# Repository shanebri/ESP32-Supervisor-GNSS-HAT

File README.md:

# ESP32 Supervisor + GNSS HAT

Raspberry Pi HAT with an ESP32-C6 supervisor, u-blox MAX-M10S GNSS receiver, and HAT ID EEPROM.

Open `hardware/Argus-RPI-HAT.kicad_pro` in KiCad 10. The folder includes the routed four-layer PCB, schematics, and custom footprints.

DRC/ERC reports are in `hardware/checks/` and use the project's configured rules. The board has not been hardware-tested; verify the fabrication stack-up and USB/GNSS impedance before ordering.

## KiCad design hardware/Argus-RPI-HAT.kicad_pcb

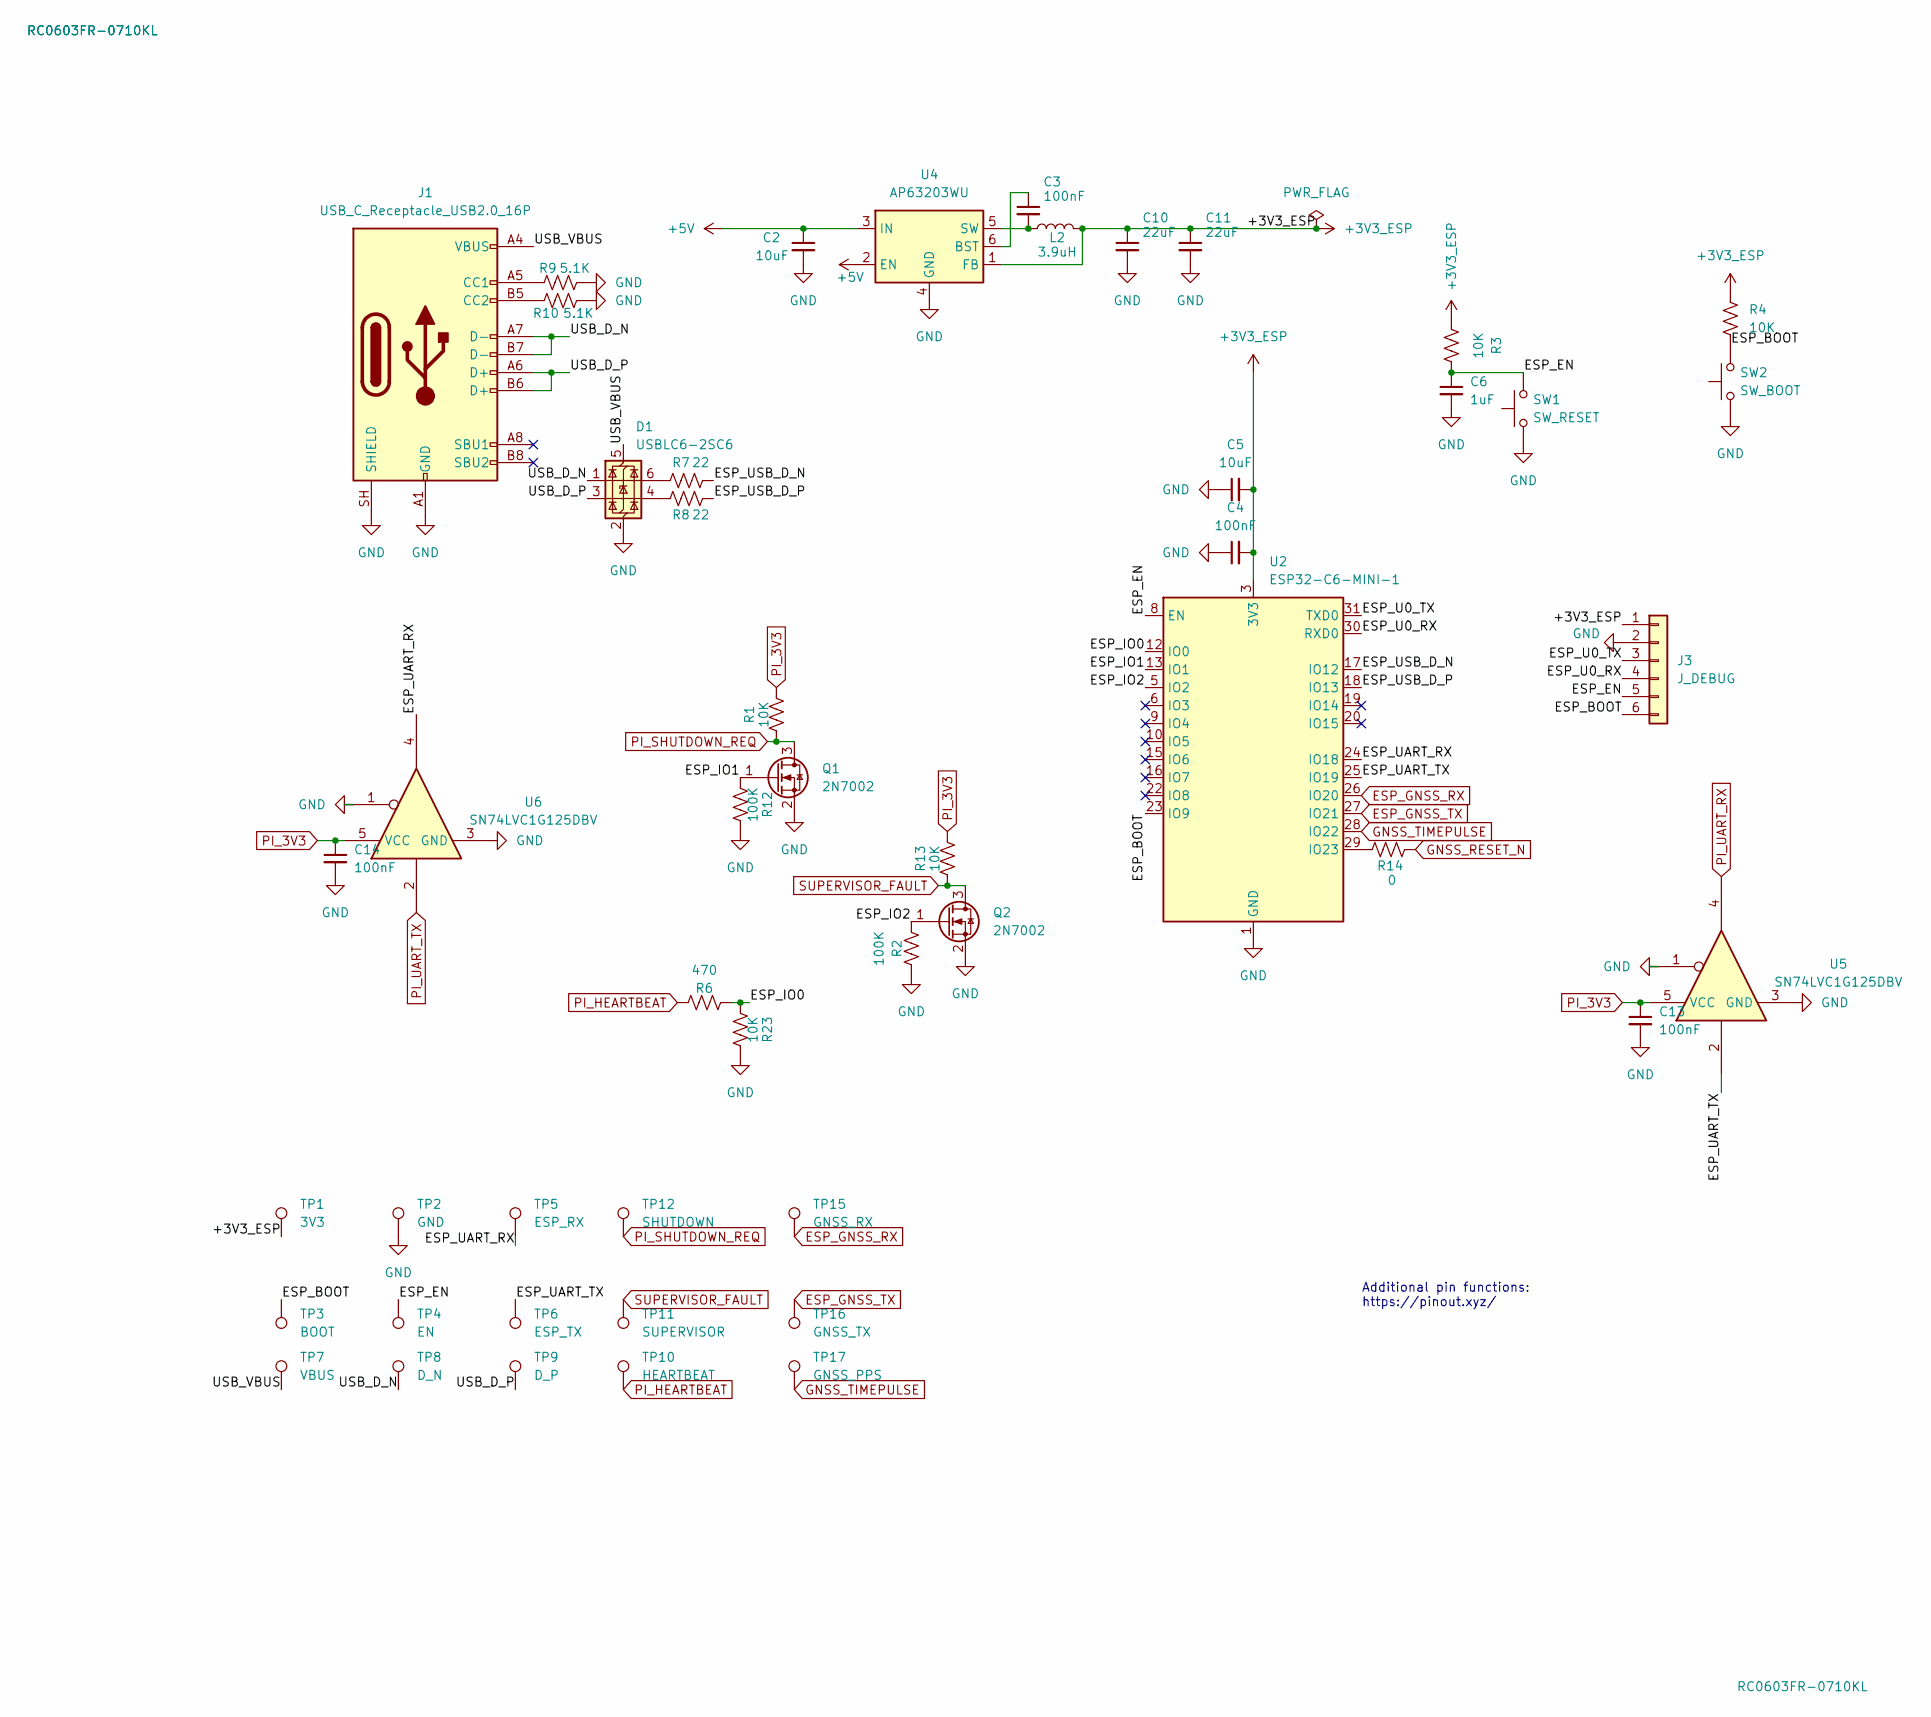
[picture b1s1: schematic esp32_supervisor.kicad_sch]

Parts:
C2: 10uF; C_0603_1608Metric; Rated Voltage 16V; Tolerance 10%; MPN GRM31CR71C106KA12L
C3, C4, C13, C14: 100nF; C_0603_1608Metric; Rated Voltage 50V; Tolerance 10%; MPN C0603C104K5RACTU
C5: 10uF; C_0805_2012Metric; Rated Voltage 10V; Tolerance 10%; MPN GRM21BR71A106KE51L
C6: 1uF; C_0603_1608Metric; Rated Voltage 16V; Tolerance 10%; MPN GRM188R71C105KA12D
C10, C11: 22uF; C_1206_3216Metric; MPN GRM31CR71A226ME15L
D1: USBLC6-2SC6; SOT-23-6; MPN USBLC6-2SC6
J1: USB_C_Receptacle_USB2.0_16P; USB_C_HRO_TYPE-C-31-M-12_EdgeSilk; MPN TYPE-C-31-M-12
J3: J_DEBUG; PinHeader_1x06_P2.54mm_Vertical; MPN TSW-106-07-G-S
L2: 3.9uH; L_Wurth_WE-PD2SR-7850
Q1, Q2: 2N7002; SOT-23; MPN 2N7002,215
R1, R3, R4, R13, R23: 10K; R_0603_1608Metric; MPN RC0603FR-0710KL
R2, R12: 100K; R_0603_1608Metric; MPN RC0603FR-07100KL
R6: 470; R_0603_1608Metric; MPN RC0603FR-07470RL
R7, R8: 22; R_0603_1608Metric; MPN RC0603FR-0722RL
R9, R10: 5.1K; R_0603_1608Metric; MPN RC0603FR-075K1L
R14: 0; R_0603_1608Metric; MPN RC0603JR-070RL
SW1: SW_RESET; SW_SPST_TL3305A; MPN TL3305AF160QG
SW2: SW_BOOT; SW_SPST_TL3305A; MPN TL3305AF160QG
TP1: 3V3; TestPoint_Pad_D1.5mm
TP2: GND; TestPoint_Pad_D1.5mm
TP3: BOOT; TestPoint_Pad_D1.5mm
TP4: EN; TestPoint_Pad_D1.5mm
TP5: ESP_RX; TestPoint_Pad_D1.5mm
TP6: ESP_TX; TestPoint_Pad_D1.5mm
TP7: VBUS; TestPoint_Pad_D1.5mm
TP8: D_N; TestPoint_Pad_D1.5mm
TP9: D_P; TestPoint_Pad_D1.5mm
TP10: HEARTBEAT; TestPoint_Pad_D1.5mm
TP11: SUPERVISOR; TestPoint_Pad_D1.5mm
TP12: SHUTDOWN; TestPoint_Pad_D1.5mm
TP15: GNSS_RX; TestPoint_Pad_D1.5mm
TP16: GNSS_TX; TestPoint_Pad_D1.5mm
TP17: GNSS_PPS; TestPoint_Pad_D1.5mm
U2: ESP32-C6-MINI-1; ESP32-C6-MINI-1_EdgeSilk; MPN ESP32-C6-MINI-1-N4
U4: AP63203WU; TSOT-23-6; MPN AP63203WU-7
U5, U6: SN74LVC1G125DBV; SOT-23-5; MPN SN74LVC1G125DBVR

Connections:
+3V3_ESP: C4.2, C5.2, C10.1, C11.1, J3.1, L2.2, R3.1, R4.1, TP1.1 (1_1), U2.3 (3V3), U4.1 (FB); also elsewhere on the board
+5V: C2.1, U4.2 (EN), U4.3 (IN); also elsewhere on the board
/esp32_supervisor/ESP_BOOT: J3.6, R4.2, SW2.2, TP3.1 (1_1), U2.23 (IO9)
/esp32_supervisor/ESP_EN: C6.1, J3.5, R3.2, SW1.2, TP4.1 (1_1), U2.8 (EN)
/esp32_supervisor/ESP_IO0: R6.1, R23.1, U2.12 (IO0)
/esp32_supervisor/ESP_IO1: Q1.1 (G), R12.1, U2.13 (IO1)
/esp32_supervisor/ESP_IO2: Q2.1 (G), R2.1, U2.5 (IO2)
/esp32_supervisor/ESP_U0_RX: J3.4, U2.30 (RXD0)
/esp32_supervisor/ESP_U0_TX: J3.3, U2.31 (TXD0)
/esp32_supervisor/ESP_UART_RX: TP5.1 (1_1), U2.24 (IO18), U6.4
/esp32_supervisor/ESP_UART_TX: TP6.1 (1_1), U2.25 (IO19), U5.2
/esp32_supervisor/ESP_USB_D_N: R7.2, U2.17 (IO12)
/esp32_supervisor/ESP_USB_D_P: R8.2, U2.18 (IO13)
/esp32_supervisor/USB_D_N: D1.1 (I/O1), J1.A7 (D-), J1.B7 (D-), TP8.1 (1_1)
/esp32_supervisor/USB_D_P: D1.3 (I/O2), J1.A6 (D+), J1.B6 (D+), TP9.1 (1_1)
/esp32_supervisor/USB_VBUS: D1.5 (VBUS), J1.A4 (VBUS), J1.A9 (VBUS), J1.B4 (VBUS), J1.B9 (VBUS), TP7.1 (1_1)
ESP_GNSS_RX: TP15.1 (1_1), U2.26 (IO20); also elsewhere on the board
ESP_GNSS_TX: TP16.1 (1_1), U2.27 (IO21); also elsewhere on the board
GND: C2.2, C4.1, C5.1, C6.2, C10.2, C11.2, C13.2, C14.2, D1.2 (GND), J1.A1 (GND), J1.A12 (GND), J1.B1 (GND), J1.B12 (GND), J1.SH (SHIELD), J3.2, Q1.2 (S), Q2.2 (S), R2.2, R9.2, R10.2, R12.2, R23.2, SW1.1, SW2.1, TP2.1 (1_1), U2.1 (GND), U2.2 (GND), U2.11 (GND), U2.14 (GND), U2.36 (GND), U2.37 (GND), U2.38 (GND), U2.39 (GND), U2.40 (GND), U2.41 (GND), U2.42 (GND), U2.43 (GND), U2.44 (GND), U2.45 (GND), U2.46 (GND), U2.47 (GND), U2.48 (GND), U2.49 (GND), U2.50 (GND), U2.51 (GND), U2.52 (GND), U2.53 (GND), U4.4 (GND), U5.1, U5.3 (GND), U6.1, U6.3 (GND); also elsewhere on the board
GNSS_RESET_N: R14.1; also elsewhere on the board
GNSS_TIMEPULSE: TP17.1 (1_1), U2.28 (IO22); also elsewhere on the board
unnamed: D1.6 (I/O1), R7.1
unnamed: D1.4 (I/O2), R8.1
unnamed: J1.A5 (CC1), R9.1
unnamed: J1.B5 (CC2), R10.1
unnamed: R14.2, U2.29 (IO23)
unnamed: C3.1, U4.6 (BST)
unnamed: C3.2, L2.1, U4.5 (SW)
PI_3V3: C13.1, C14.1, R1.2, R13.2, U5.5 (VCC), U6.5 (VCC); also elsewhere on the board
PI_HEARTBEAT: R6.2, TP10.1 (1_1); also elsewhere on the board
PI_SHUTDOWN_REQ: Q1.3 (D), R1.1, TP12.1 (1_1); also elsewhere on the board
PI_UART_RX: U5.4; also elsewhere on the board
PI_UART_TX: U6.2; also elsewhere on the board
SUPERVISOR_FAULT: Q2.3 (D), R13.1, TP11.1 (1_1); also elsewhere on the board

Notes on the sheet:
Additional pin functions: https://pinout.xyz/

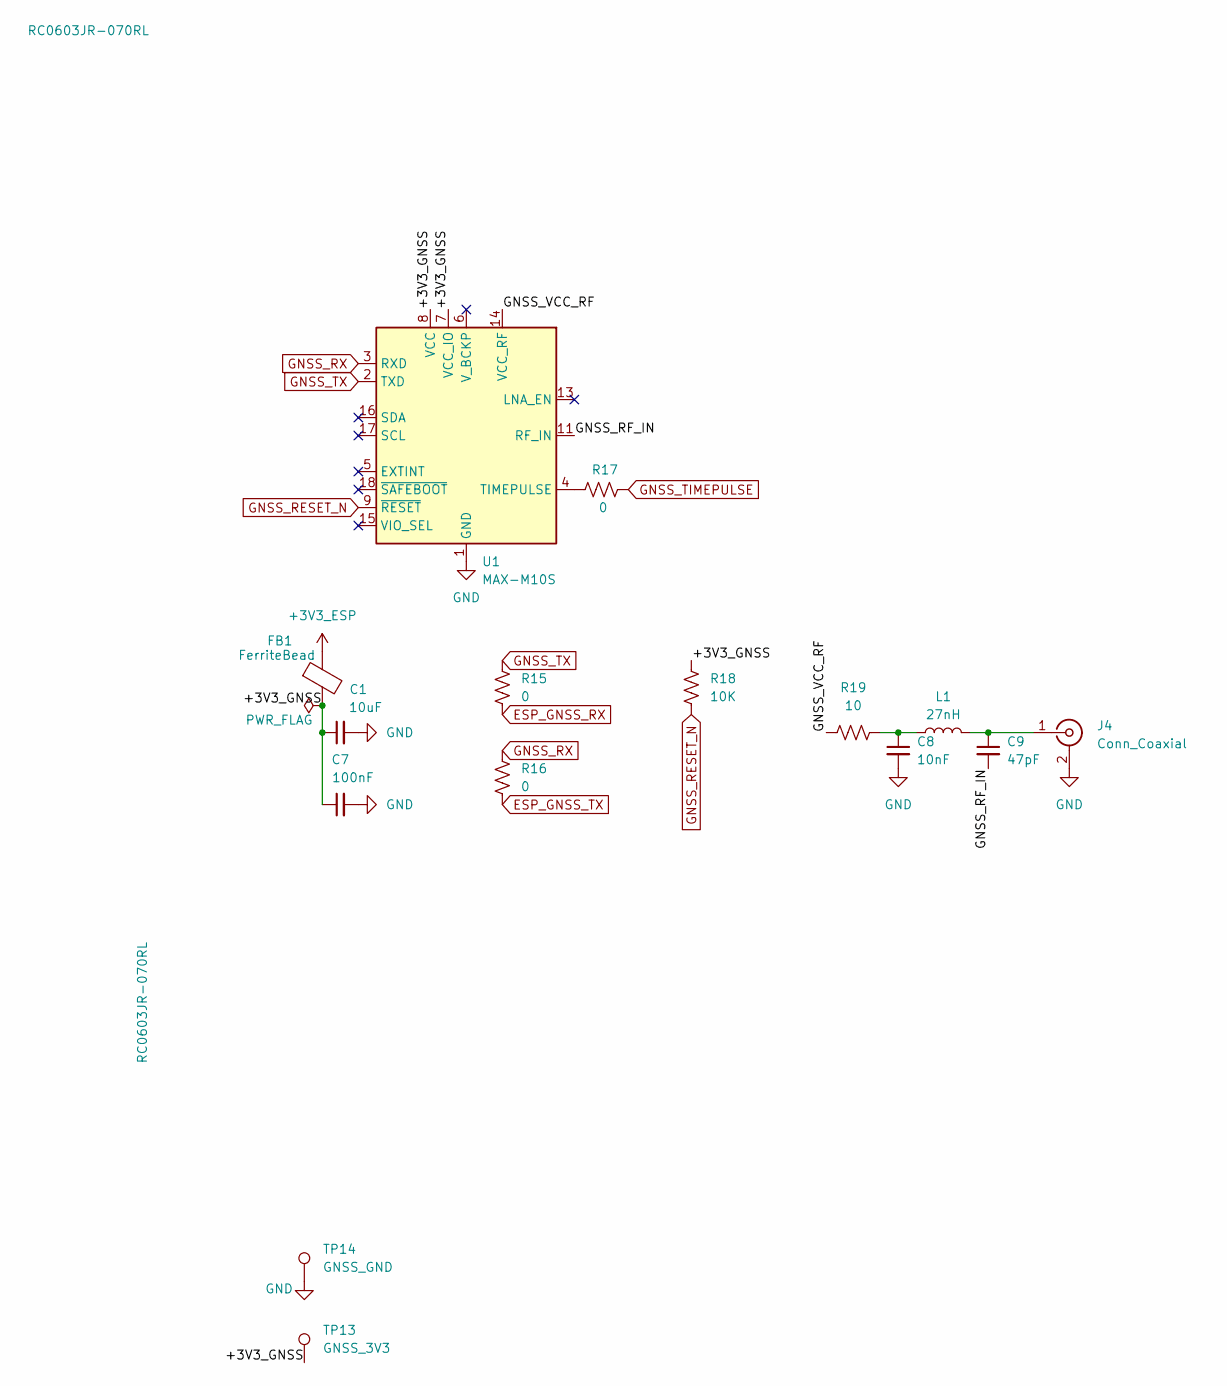
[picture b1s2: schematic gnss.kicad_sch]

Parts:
C1: 10uF; C_0805_2012Metric; Rated Voltage 10V; Tolerance 10%; MPN GRM21BR71A106KE51L
C7: 100nF; C_0603_1608Metric; Rated Voltage 50V; Tolerance 10%; MPN C0603C104K5RACTU
C8: 10nF; C_0603_1608Metric; Rated Voltage 50V; Tolerance 10%; MPN C0603C103K5RACTU
C9: 47pF; C_0603_1608Metric; Rated Voltage 50V; Tolerance 5%; MPN C0603C470J5GACTU
FB1: FerriteBead; R_0603_1608Metric; MPN BLM18KG121JH1D
J4: Conn_Coaxial; U.FL_Hirose_U.FL-R-SMT-1_Vertical; MPN U.FL-R-SMT-1(60)
L1: 27nH; L_0603_1608Metric; Tolerance 5%; Curent Rating > 300mA; MPN LQW18AN27NJ00D
R15, R16, R17: 0; R_0603_1608Metric; MPN RC0603JR-070RL
R18: 10K; R_0603_1608Metric; MPN RC0603FR-0710KL
R19: 10; R_0603_1608Metric; Tolerance 5%; Power Rating 0.25W; MPN RC0603FR-0710RL
TP13: GNSS_3V3; TestPoint_Pad_D1.5mm
TP14: GNSS_GND; TestPoint_Pad_D1.5mm
U1: MAX-M10S; ublox_MAX; MPN MAX-M10S-00B-01

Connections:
+3V3_ESP: FB1.1; also elsewhere on the board
/gnss/+3V3_GNSS: C1.1, C7.1, FB1.2, R18.1, TP13.1 (1_1), U1.7 (VCC_IO), U1.8 (VCC)
/gnss/GNSS_RF_IN: C9.2, U1.11 (RF_IN)
/gnss/GNSS_VCC_RF: R19.1, U1.14 (VCC_RF)
ESP_GNSS_RX: R15.2; also elsewhere on the board
ESP_GNSS_TX: R16.2; also elsewhere on the board
GND: C1.2, C7.2, C8.2, J4.2 (Ext), TP14.1 (1_1), U1.1 (GND), U1.10 (GND), U1.12 (GND); also elsewhere on the board
GNSS_RESET_N: R18.2, U1.9 (~RESET); also elsewhere on the board
GNSS_RX: R16.1, U1.3 (RXD)
GNSS_TIMEPULSE: R17.2; also elsewhere on the board
GNSS_TX: R15.1, U1.2 (TXD)
unnamed: C8.1, L1.1, R19.2
unnamed: C9.1, J4.1 (In), L1.2
unnamed: R17.1, U1.4 (TIMEPULSE)

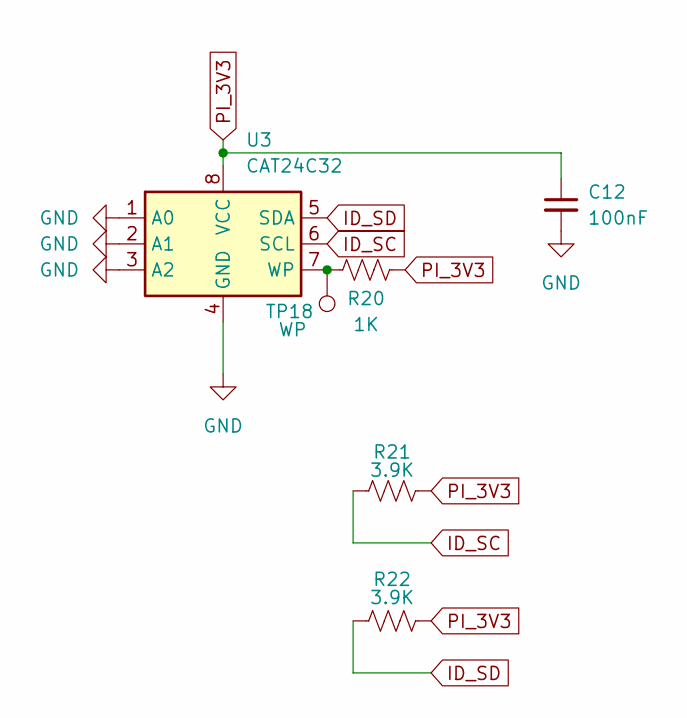
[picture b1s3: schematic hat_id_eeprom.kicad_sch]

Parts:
C12: 100nF; C_0603_1608Metric; Rated Voltage 50V; Tolerance 10%; MPN C0603C104K5RACTU
R20: 1K; R_0603_1608Metric
R21, R22: 3.9K; R_0603_1608Metric; MPN RC0603FR-073K9L
TP18: WP; TestPoint_Pad_D1.5mm
U3: CAT24C32; TSSOP-8_4.4x3mm_P0.65mm; MPN CAT24C32YI-GT3

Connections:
GND: C12.2, U3.1 (A0), U3.2 (A1), U3.3 (A2), U3.4 (GND); also elsewhere on the board
ID_SC: R21.1, U3.6 (SCL); also elsewhere on the board
ID_SD: R22.1, U3.5 (SDA); also elsewhere on the board
unnamed: R20.1, TP18.1 (1_1), U3.7 (WP)
PI_3V3: C12.1, R20.2, R21.2, R22.2, U3.8 (VCC); also elsewhere on the board

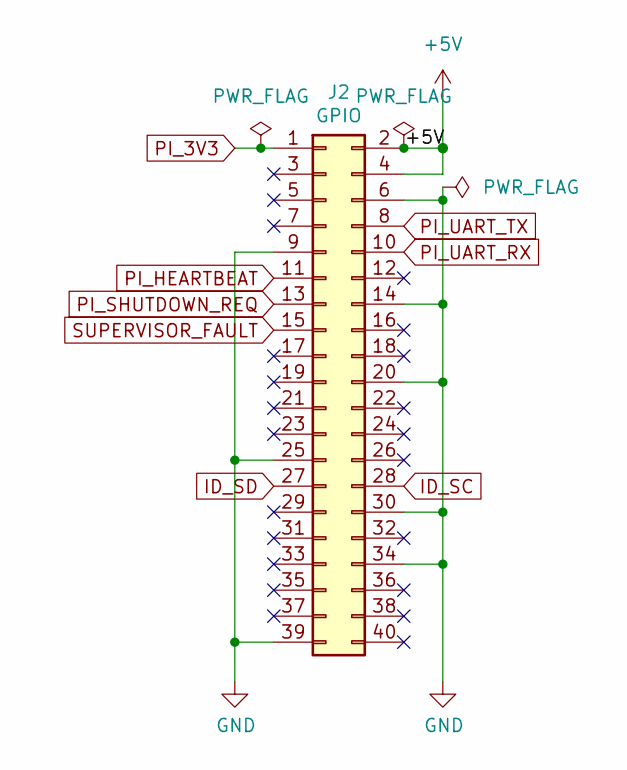
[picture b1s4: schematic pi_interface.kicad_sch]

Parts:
J2: GPIO; PinSocket_2x20_P2.54mm_Vertical; MPN ESQ-120-23-G-D

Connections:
+5V: J2.2, J2.4; also elsewhere on the board
GND: J2.6, J2.9, J2.14, J2.20, J2.25, J2.30, J2.34, J2.39; also elsewhere on the board
ID_SC: J2.28; also elsewhere on the board
ID_SD: J2.27; also elsewhere on the board
PI_3V3: J2.1; also elsewhere on the board
PI_HEARTBEAT: J2.11; also elsewhere on the board
PI_SHUTDOWN_REQ: J2.13; also elsewhere on the board
PI_UART_RX: J2.10; also elsewhere on the board
PI_UART_TX: J2.8; also elsewhere on the board
SUPERVISOR_FAULT: J2.15; also elsewhere on the board

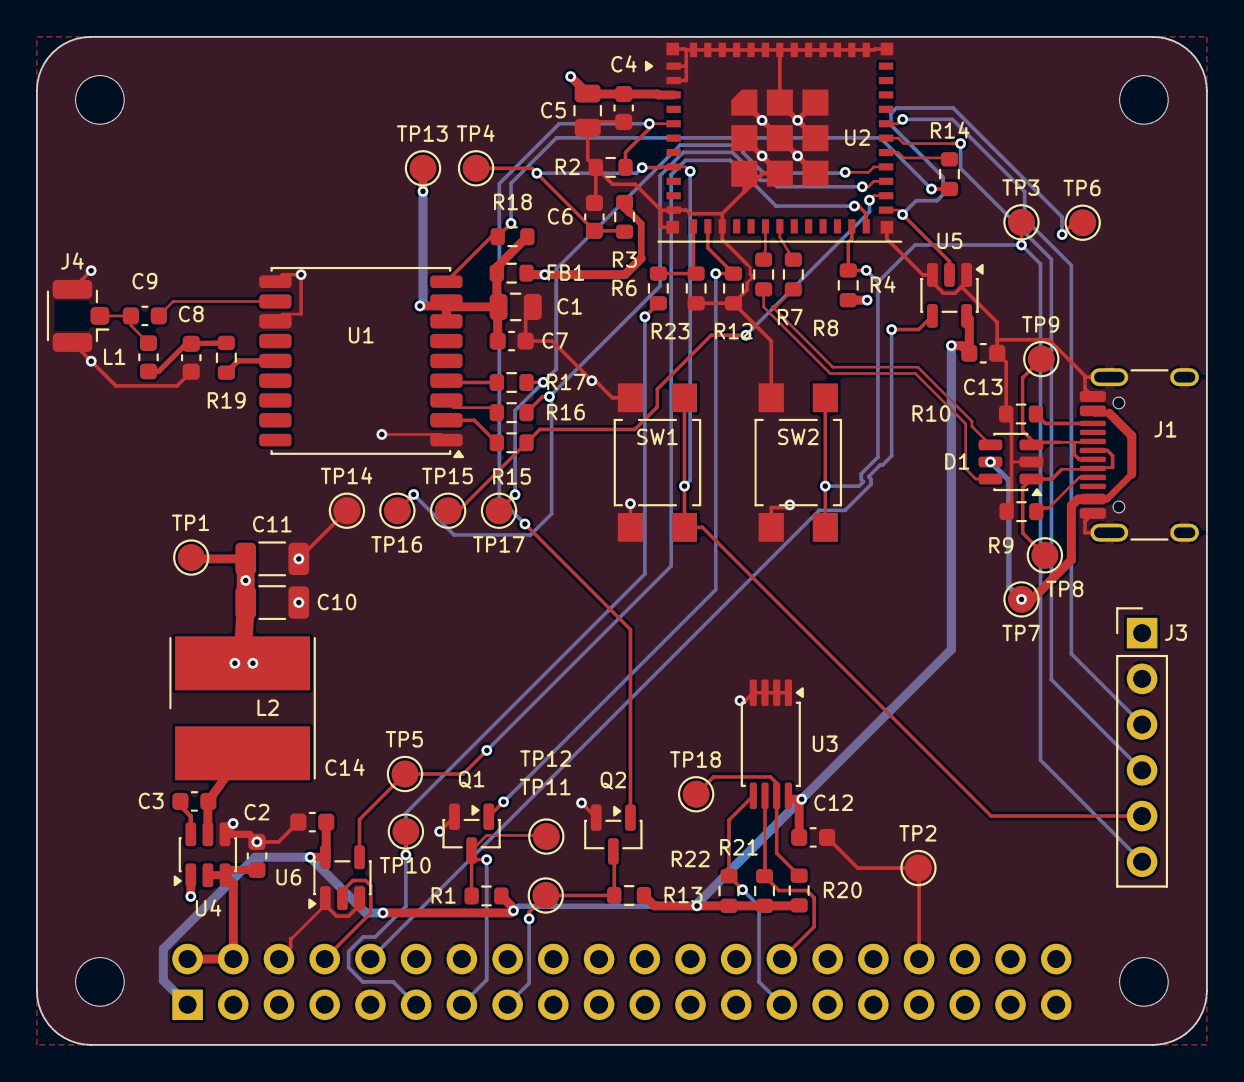
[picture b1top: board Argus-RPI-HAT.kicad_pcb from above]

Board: 4 copper layers, 65.0 x 56.0 mm, 75 parts (1 on the bottom side), 45 nets.

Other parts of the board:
MH1, MH2, MH3, MH4: MountingHole_2.7mm_M2.5
